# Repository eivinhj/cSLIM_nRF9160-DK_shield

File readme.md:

Shield design files of cSLIM shield hardware for nRF9160-DK.

Edit using KiCad: https://www.kicad.org/

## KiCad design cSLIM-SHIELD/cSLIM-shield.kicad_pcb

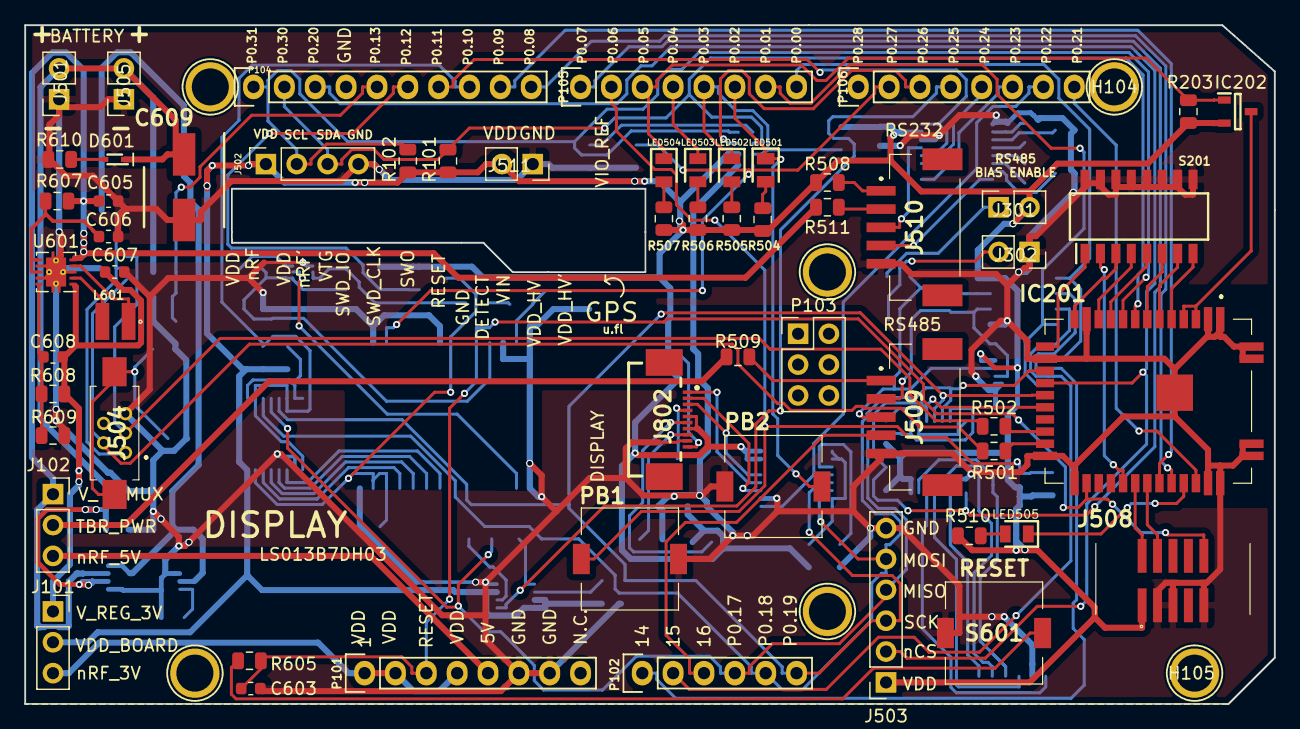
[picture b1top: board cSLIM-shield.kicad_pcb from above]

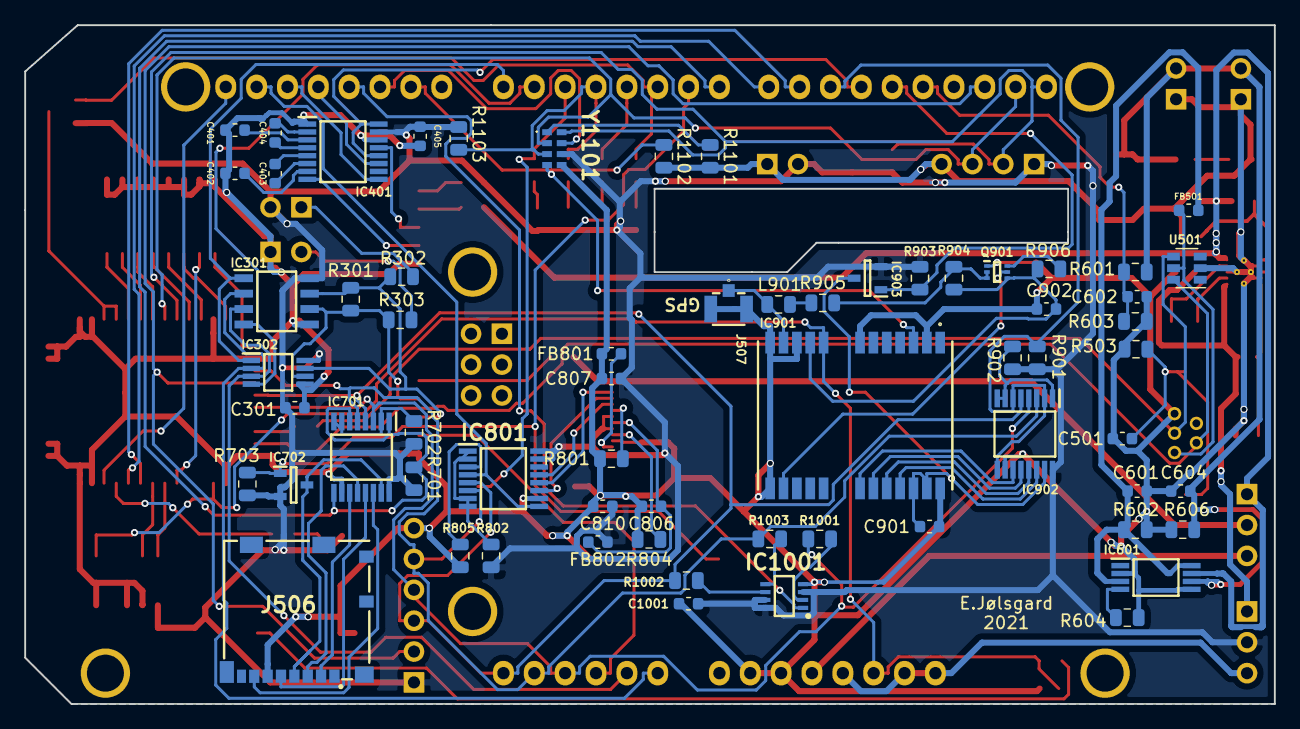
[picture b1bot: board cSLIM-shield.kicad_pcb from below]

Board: 2 copper layers, 102.9 x 55.9 mm, 128 parts (64 on the bottom side), 116 nets.

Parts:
C301, C401, C402, C403, C404, C405, C601, C604, C606, C806, C810, C901, C1001: 100nF; C_0603_1608Metric
C501: 12pF; C_0603_1608Metric
C602, C603, C902: 1uF; C_0603_1608Metric
C605: 10uF; C_0603_1608Metric
C607: 22uF; C_0603_1608Metric
C608: 1.8pF; C_0603_1608Metric
C609: PCH1E101MCL4GS; CAPAE660X840N
C807: 1uF/50V; C_0603_1608Metric
D601: 1SS390SMFHT2R; SODFL1608X70N
FB501: 500mA; C_0603_1608Metric
FB801, FB802: Ferrite_Bead; C_0603_1608Metric
H101, H102, H103, H104, H105, H106: CONN_01X01; Arduino_1pin
IC201: WLR089U0-I_RM; WLR089U0IRM
IC202, IC702, IC903: NX2301P,215; SOT95P230X110-3N
IC301: MAX3486ESA+; SOIC127P600X175-8N
IC302: MAX3471EUA+; SOP65P490X110-8N
IC401: MAX3221CUE+; SOP65P640X110-16N
IC601: TPS2113PWR; SOP65P640X120-8N
IC701, IC801, IC902: SN74AVC4T774PWR; SOP65P640X120-16N
IC901: NEO-M9N-00B; NEO-M8T
IC1001: CY15B108QN-20LPXC; SON65P323X328X55-8N
J101, J102: Conn_01x03_Male; PinSocket_1x03_P2.54mm_Vertical
J301, J302, J501, J505, J511: Conn_01x02_Male; PinSocket_1x02_P2.54mm_Vertical
J502: Conn_01x04; PinSocket_1x04_P2.54mm_Vertical
J503: Conn_01x06; PinSocket_1x06_P2.54mm_Vertical
J504: 10119313-302TLF; 10119313302TLF
J506: 104031-0811; 1040310811
J507: CONUFL001-SMD-T; CONUFL001-SMD
J508: SHF-105-01-L-D-SM; SHF-105-01-X-D-SM
J509, J510: BM05B-ZESS-TBT__LF__SN_; BM05BZESSTBTLFSN
J802: 52746-1071
L601: LPS3015-222MRB; LPS3015
L901: L; L_0805_2012Metric
LED501: APT2012LSECK_J3-PRV; LEDC2012X75N
LED502: APT2012LSYCK_J3-PRV; LEDC2012X85N
LED503: APT2012LZGCK; LEDC2012X85N
LED504, LED505: APT2012LVBC_D; LEDC2012X85N
P101: Power; Socket_Strip_Arduino_1x08
P102: Analog; Socket_Strip_Arduino_1x06
P103: Conn_02x03_Odd_Even; PinHeader_2x03_P2.54mm_Vertical
P104: Digital; Socket_Strip_Arduino_1x10
P105, P106: Digital; Socket_Strip_Arduino_1x08
PB1, PB2: TLS_A_070J_LFS; TLSA070JLFS
Q901: SI1040X-T1-GE3; SOTFL50P160X60-6N
R101, R102: 4.7k; R_0805_2012Metric
R203, R603, R701, R702, R703, R801, R802, R804, R805, R901, R902, R903, R906, R1102, R1103: 100k; R_0805_2012Metric
R301: 120R; R_0805_2012Metric
R302, R303: 680R; R_0805_2012Metric
R501, R502: 15R; R_0805_2012Metric
R503, R508, R509, R511, R904: 0R; R_0805_2012Metric
R504, R505: 820R; R_0805_2012Metric
R506, R507, R510: 330R; R_0805_2012Metric
R601, R609: 240k; R_0805_2012Metric
R602, R606: 1M; R_0805_2012Metric
R604: 390R; R_0805_2012Metric
R605: 1k; R_0805_2012Metric
R607: 100R; R_0805_2012Metric
R608: 1M2; R_0805_2012Metric
R610: 3k; R_0805_2012Metric
R905: 10R; R_0805_2012Metric
R1001, R1002: 33R; R_0805_2012Metric
R1003: 50R; R_0805_2012Metric
R1101: 10k; R_0805_2012Metric
S201: 97C08ST; SOIC127P671X170-16N
S601: TLS_A_070J_LFS; TLSA070JLFS
U501: USBLC6-2SC6; SOT-23-6
U601: TPS63000; Texas_DRC0010J_ThermalVias
Y1101: RV-3032-C7-TA-QC; RV3032C7TAQA

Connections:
+BATT: C604.1, C609.1, D601.1, IC601.6, J501.2, J505.2, R601.2, R606.1
/9 cSLIM Connectors/GPS_ANTENNA: IC901.11, J507.1, L901.1
/9 cSLIM Connectors/LoRa_SWDCLK: IC201.30, J508.4
/9 cSLIM Connectors/LoRa_SWDIO: IC201.29, J508.2
/9 cSLIM Connectors/RS232_RX: IC401.8, J510.4
/9 cSLIM Connectors/RS232_TX: IC401.13, J510.3
/9 cSLIM Connectors/RS485_A: IC301.6, IC302.6, J509.2, R301.2, R303.1
/9 cSLIM Connectors/RS485_B: IC301.7, IC302.7, J509.3, R301.1, R302.2
/9 cSLIM Connectors/USB_N: J504.2, R501.1, U501.6
/9 cSLIM Connectors/USB_P: J504.3, R502.1, U501.4
/9 cSLIM Connectors/uSD_CLK: IC701.13, J506.5
/9 cSLIM Connectors/uSD_MISO: IC701.14, J506.7
/9 cSLIM Connectors/uSD_MOSI: IC701.12, J506.3
/9 cSLIM Connectors/uSD_VDD: IC701.15, IC702.3, J506.4
/9 cSLIM Connectors/uSD_nCS: IC701.11, J506.2
/GPS_TIMEPULSE: IC901.3, P106.2, R1102.2, Y1101.4
/I2C_SCL: IC201.9, J502.2, P104.1, R102.1, Y1101.8
/I2C_SDA: IC201.8, J502.3, P104.2, R101.1, Y1101.2
/LoRa_nRESET: C603.1, IC201.25, IC901.8, J508.10, P101.3, R605.1
/P0.00: IC301.1, IC302.1, P105.8
/P0.01: IC301.4, IC302.4, P105.7
/P0.02: LED501.1, P105.6, PB2.1
/P0.03: LED502.1, P105.5, R1103.1, Y1101.3
/P0.04: LED503.1, P105.4
/P0.05: IC202.1, LED504.1, P105.3, R203.1
/P0.06: IC702.1, P105.2, PB1.1, R703.1
/P0.07: IC701.1, IC701.6, IC701.9, P105.1, R701.1
/P0.08: IC201.32, P104.10
/P0.09: IC201.31, P104.9
/P0.10: IC902.2, IC902.6, IC902.9, P104.8, R901.1
/P0.11: IC401.12, IC401.16, P104.7
/P0.12: IC903.1, P104.6, R903.1
/P0.13: C602.1, P104.5, R601.1, R603.1
/P0.14: IC301.2, IC302.2, P102.1
/P0.15: IC301.3, IC302.3, P102.2
/P0.16: J509.4, P102.3
/P0.17: IC201.19, IC701.3, IC902.4, J503.4, P102.4, R1001.1
/P0.18: IC201.16, IC701.5, IC801.6, IC902.3, J503.5, P102.5, R1003.1
/P0.19: IC201.18, IC701.4, IC801.5, IC902.5, J503.3, P102.6, R1002.1
/P0.20: IC201.17, J503.2, P104.3
/P0.21: IC201.34, P106.8
/P0.22: IC801.4, IC801.9, P106.7
/P0.23: IC401.9, P106.6
/P0.24: IC401.11, P106.5
/P0.25: IC1001.1, P106.4
/P0.26: P106.3, Y1101.7
/TBR_PWR: J102.2, R509.2
/USB_VBUS: C601.1, FB501.1, IC601.3, IC601.8, R602.1
/V_MUX_OUT: C605.1, IC601.7, J102.1, R511.2, R607.2, U601.5
/V_nRF_3V: J101.3, P101.1, P101.2, P101.4
/V_nRF_5V: J102.3, P101.5
/V_reg: C607.1, C608.1, J101.1, R608.1, U601.1
/cSLIM Display/MOSI: IC801.11, J802.2
/cSLIM Display/SCK: IC801.12, J802.1
/cSLIM Display/nCS: IC801.13, J802.3
/cSLIM GPS External/ANT_ON: IC901.14, Q901.5
/cSLIM GPS External/GPS_MISO: IC901.20, IC902.13
/cSLIM GPS External/GPS_MOSI: IC901.21, IC902.14
/cSLIM GPS External/GPS_SCK: IC901.19, IC902.12
/cSLIM GPS External/GPS_VDD: C901.1, IC901.22, IC901.23, IC902.15, IC903.3
/cSLIM GPS External/GPS_nCS: IC901.18, IC902.11
/cSLIM LoRa/AD1: IC201.14, S201.1
/cSLIM LoRa/AD2: IC201.28, S201.2
/cSLIM LoRa/AD3: IC201.13, S201.3
/cSLIM LoRa/AD4: IC201.11, S201.4
/cSLIM LoRa/AD5: IC201.10, S201.5
/cSLIM LoRa/AD6: IC201.7, S201.6
/cSLIM LoRa/AD7: IC201.6, S201.7
/cSLIM LoRa/AD8: IC201.5, S201.8
/cSLIM LoRa/LoRa_USB_DM: IC201.22, R501.2
/cSLIM LoRa/LoRa_USB_DP: IC201.21, R502.2
/cSLIM LoRa/PB03: IC201.33, LED505.1
/cSLIM RS232/C1+: C404.1, IC401.2
/cSLIM RS232/C1-: C404.2, IC401.4
/cSLIM RS232/C2+: C403.1, IC401.5
/cSLIM RS232/C2-: C403.2, IC401.6
/cSLIM RS232/V+: C401.1, IC401.3
/cSLIM RS232/V-: C402.1, IC401.7
GND: C301.2, C401.2, C402.2, C405.2, C501.2, C601.2, C602.2, C603.2, C604.2, C605.2, C606.2, C607.2, C609.2, C806.2, C807.2, C810.2, C901.2, C902.2, C1001.2, FB801.2, IC201.1, IC201.2, IC201.12, IC201.15, IC201.23, IC201.24, IC201.35, IC201.36, IC201.37, IC201.38, IC201.39, IC201.40, IC201.41, IC301.5, IC302.5, IC401.1, IC401.14, IC601.2, IC601.5, IC701.10, IC801.10, IC901.2, IC901.7, IC901.10, IC901.12, IC901.13, IC901.24, IC902.10, IC1001.4, J302.1, J501.1, J502.4, J503.6, J504.5, J505.1, J506.6, J507.2, J507.3, J508.3, J508.5, J508.9, J509.5, J510.5, J511.1, J802.9, P101.6, P101.7, PB1.2, PB2.2, Q901.1, R503.2, R602.2, R603.2, R604.2, R606.2, R609.2, R610.2, R801.2, R804.2, R805.2, R1101.2, R1102.1, S201.9, S201.10, S201.11, S201.12, S201.13, S201.14, S201.15, S201.16, S601.2, U501.2, U601.3, U601.7, U601.9, U601.11, Y1101.5
unnamed: C501.1, J504.MP1, J504.MP2, R503.1
unnamed: C606.1, R607.1, U601.6, U601.8
unnamed: C608.2, R608.2, R609.1, U601.10
unnamed: C806.1, FB802.2, J802.6
unnamed: C902.1, IC901.9, Q901.4, R904.2, R906.2
unnamed: D601.2, R610.1
unnamed: FB501.2, J504.1, U501.5
unnamed: FB801.1, J802.10
unnamed: IC201.3, IC201.4, IC202.3
unnamed: IC601.4, R604.1
unnamed: IC701.2, IC701.7, IC701.8, R702.1
unnamed: IC801.1, IC801.2, IC801.7, IC801.8, R802.1
unnamed: IC801.3, R805.1
unnamed: IC902.1, IC902.7, IC902.8, R902.1
unnamed: IC1001.2, R1001.2
unnamed: IC1001.5, R1003.2
unnamed: IC1001.6, R1002.2
unnamed: J301.1, R302.1
unnamed: J302.2, R303.2
unnamed: J509.1, R509.1
unnamed: J510.1, R508.1
unnamed: J510.2, R511.1
unnamed: J802.4, R801.1
unnamed: J802.8, R804.1
unnamed: L601.1, U601.4
unnamed: L601.2, U601.2
unnamed: L901.2, R905.2
unnamed: LED501.2, R504.1
unnamed: LED502.2, R505.1
unnamed: LED503.2, R506.1
unnamed: LED504.2, R507.1
unnamed: LED505.2, R510.1
unnamed: Q901.2, Q901.3, R904.1, R905.1
unnamed: Q901.6, R906.1
unnamed: R605.2, S601.1
unnamed: R1101.1, Y1101.1
VDD: C301.1, C405.1, C807.1, C810.1, C1001.1, FB802.1, IC202.2, IC301.8, IC302.8, IC401.15, IC701.16, IC702.2, IC801.15, IC801.16, IC902.16, IC903.2, IC1001.3, IC1001.7, IC1001.8, J101.2, J301.2, J502.1, J503.1, J508.1, J511.2, J802.5, J802.7, R101.2, R102.2, R203.2, R504.2, R505.2, R506.2, R507.2, R508.2, R510.2, R701.2, R702.2, R703.2, R802.2, R901.2, R902.2, R903.2, R1103.2, Y1101.6

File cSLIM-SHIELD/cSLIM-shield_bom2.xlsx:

Id | Designator | Package | Quantity | Designation | Supplier and ref | OK?
1 | R801,R603,R701,R702,R703,R901,R902,R903,R906,R802,R803,R203,R804,R805,R1102,R11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 | R_0805_2012Metric | 16 | 100k | M
2 | P101 | Socket_Strip_Arduino_1x08 | 1 | Power | M
3 | P102 | Socket_Strip_Arduino_1x06 | 1 | Analog | M
4 | P104 | Socket_Strip_Arduino_1x10 | 1 | Digital | M
5 | P105,P106 | Socket_Strip_Arduino_1x08 | 2 | Digital | M
6 | H101,H102,H103,H106,H104,H105 | Arduino_1pin | 6 | CONN_01X01 | DNP
7 | P103 | PinHeader_2x03_P2.54mm_Vertical | 1 | Conn_02x03_Odd_Even | M
8 | C301,C401,C402,C403,C404,C405,C601,C604,C606,C901,C1001,C806,C810 | C_0603_1608Metric | 13 | 100nF | M
9 | C501 | C_0603_1608Metric | 1 | 12pF | M
10 | C602,C603,C902 | C_0603_1608Metric | 3 | 1uF | M
11 | C605 | C_0603_1608Metric | 1 | 10uF | M
12 | C607 | C_0603_1608Metric | 1 | 22uF | M
13 | FB501 | C_0603_1608Metric | 1 | 500mA | M
14 | IC201 | WLR089U0IRM | 1 | WLR089U0-I_RM | M
15 | IC301 | SOIC127P600X175-8N | 1 | MAX3486ESA+ | M
16 | IC302 | SOP65P490X110-8N | 1 | MAX3471EUA+ | DNP
17 | IC401 | SOP65P640X110-16N | 1 | MAX3221CUE+ | M
18 | IC601 | SOP65P640X120-8N | 1 | TPS2113PWR | M
19 | IC701,IC902,IC801 | SOP65P640X120-16N | 3 | SN74AVC4T774PWR | M
20 | IC702,IC903,IC802,IC202 | SOT95P230X110-3N | 4 | NX2301P,215 | M
21 | IC901 | NEO-M8T | 1 | NEO-M9N-00B | Best.tdl
22 | J101,J102 | PinSocket_1x03_P2.54mm_Vertical | 2 | Conn_01x03_Male
23 | J501,J505,J511 | PinSocket_1x02_P2.54mm_Vertical | 3 | Conn_01x02_Male | M
24 | J502 | PinSocket_1x04_P2.54mm_Vertical | 1 | Conn_01x04 | M
25 | J503 | PinSocket_1x06_P2.54mm_Vertical | 1 | Conn_01x06 | M
26 | J506 | 1040310811 | 1 | 104031-0811 | M
27 | J507 | CONUFL001-SMD | 1 | CONUFL001-SMD-T | https://www.digikey.no/product-detail/en/linx-technologies-i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
28 | J508 | SHF-105-01-X-D-SM | 1 | SHF-105-01-L-D-SM | 1
29 | J509,J510 | BM05BZESSTBTLFSN | 2 | BM05B-ZESS-TBT__LF__SN_ | https://no.farnell.com/jst-japan-solderless-terminals/bm05b-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
30 | L601 | LPS3015 | 1 | LPS3015-222MRB | M
31 | L901 | L_0805_2012Metric | 1 | L | DNP
32 | LED501 | LEDC2012X75N | 1 | APT2012LSECK_J3-PRV | M
33 | LED502 | LEDC2012X85N | 1 | APT2012LSYCK_J3-PRV | M
34 | LED503 | LEDC2012X85N | 1 | APT2012LZGCK | M
35 | LED504,LED505 | LEDC2012X85N | 2 | APT2012LVBC_D | M
36 | Q901 | SOTFL50P160X60-6N | 1 | SI1040X-T1-GE3 | DNP
37 | R301 | R_0805_2012Metric | 1 | 120R | M
38 | R501,R502 | R_0805_2012Metric | 2 | 15R | M
39 | R503,R508,R509,R904,R511 | R_0805_2012Metric | 5 | 0R | M
40 | R504,R505 | R_0805_2012Metric | 2 | 820R | M
41 | R506,R507,R510 | R_0805_2012Metric | 3 | 330R | M
42 | R601,R609 | R_0805_2012Metric | 2 | 240k | M
43 | R602,R606 | R_0805_2012Metric | 2 | 1M | M
44 | R604 | R_0805_2012Metric | 1 | 390R | M
45 | R605 | R_0805_2012Metric | 1 | 1k | M
46 | R607 | R_0805_2012Metric | 1 | 100R | M
47 | R608 | R_0805_2012Metric | 1 | 1M2 | M
48 | R905 | R_0805_2012Metric | 1 | 10R | M
49 | R1001,R1002 | R_0805_2012Metric | 2 | 33R | M
50 | R1003 | R_0805_2012Metric | 1 | 50R | M
51 | S201 | SOIC127P671X170-16N | 1 | 97C08ST | M
52 | S601,PB1,PB2 | TLSA070JLFS | 3 | TLS_A_070J_LFS | M
53 | U501 | SOT-23-6 | 1 | USBLC6-2SC6 | M
54 | U601 | Texas_DRC0010J_ThermalVias | 1 | TPS63000 | M
55 | C608 | C_0603_1608Metric | 1 | 1.8pF | M
56 | C807 | C_0603_1608Metric | 1 | 1uF/50V | M
57 | FB801,FB802 | C_0603_1608Metric | 2 | Ferrite_Bead | M
58 | J504 | 10119313302TLF | 1 | 10119313-302TLF | M
59 | J802 | 52746-1071 | 1 | 52746-1071 | M
60 | R101,R102 | R_0805_2012Metric | 2 | 4.7k | M
61 | R1101 | R_0805_2012Metric | 1 | 10k | M
62 | Y1101 | RV3032C7TAQA | 1 | RV-3032-C7-TA-QC
63 | IC1001 | SON65P323X328X55-8N | 1 | CY15B108QN-20LPXC | M
Extra
 |  | Wires for RS485 RS232 | 25 |  | https://no.rs-online.com/web/p/pre-crimped-leads/8201396/
 |  | Housing for connectors | 10 |  | https://no.rs-online.com/web/p/wire-housings-plugs/8201365/?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
 |  | GPS-antenna
 |  | LoRa-antenna
 |  | RS485-Wet cable connector
 |  | u.fl to screw terminal
 |  | vanntett boks
 |  | Batteri
 |  | Antennekabel

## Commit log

2021-08-10 Add to Git
